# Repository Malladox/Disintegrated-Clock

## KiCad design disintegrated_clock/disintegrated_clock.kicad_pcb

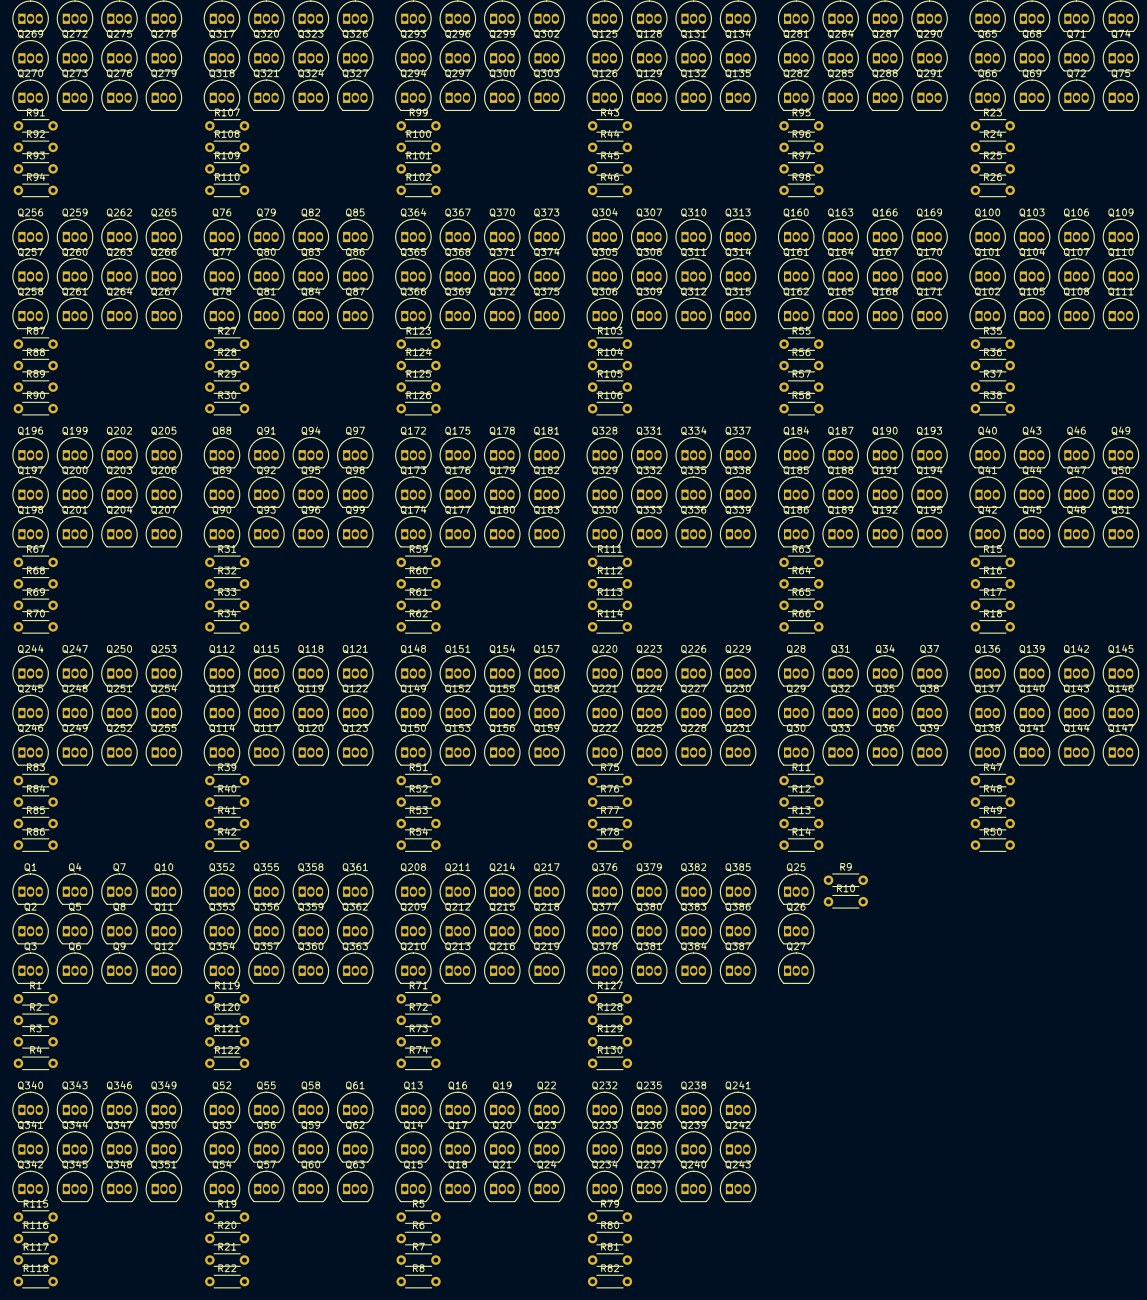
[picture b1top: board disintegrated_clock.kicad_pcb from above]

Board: 2 copper layers, 517 parts (0 on the bottom side), 421 nets, no tracks yet.

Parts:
Q1, Q2, Q3, Q4, Q5, Q6, Q7, Q8, Q9, Q10, Q11, Q12, Q13, Q14, Q15, Q16, Q17, Q18, Q19, Q20, Q21, Q22, Q23, Q24, Q25, Q26, Q27, Q28, Q29, Q30, Q31, Q32, Q33, Q34, Q35, Q36, Q37, Q38, Q39, Q40, Q41, Q42, Q43, Q44, Q45, Q46, Q47, Q48, Q49, Q50, Q51, Q52, Q53, Q54, Q55, Q56, Q57, Q58, Q59, Q60, Q61, Q62, Q63, Q64, Q65, Q66, Q67, Q68, Q69, Q70, Q71, Q72, Q73, Q74, Q75, Q76, Q77, Q78, Q79, Q80, Q81, Q82, Q83, Q84, Q85, Q86, Q87, Q88, Q89, Q90, Q91, Q92, Q93, Q94, Q95, Q96, Q97, Q98, Q99, Q100, Q101, Q102, Q103, Q104, Q105, Q106, Q107, Q108, Q109, Q110, Q111, Q112, Q113, Q114, Q115, Q116, Q117, Q118, Q119, Q120, Q121, Q122, Q123, Q124, Q125, Q126, Q127, Q128, Q129, Q130, Q131, Q132, Q133, Q134, Q135, Q136, Q137, Q138, Q139, Q140, Q141, Q142, Q143, Q144, Q145, Q146, Q147, Q148, Q149, Q150, Q151, Q152, Q153, Q154, Q155, Q156, Q157, Q158, Q159, Q160, Q161, Q162, Q163, Q164, Q165, Q166, Q167, Q168, Q169, Q170, Q171, Q172, Q173, Q174, Q175, Q176, Q177, Q178, Q179, Q180, Q181, Q182, Q183, Q184, Q185, Q186, Q187, Q188, Q189, Q190, Q191, Q192, Q193, Q194, Q195, Q196, Q197, Q198, Q199, Q200, Q201, Q202, Q203, Q204, Q205, Q206, Q207, Q208, Q209, Q210, Q211, Q212, Q213, Q214, Q215, Q216, Q217, Q218, Q219, Q220, Q221, Q222, Q223, Q224, Q225, Q226, Q227, Q228, Q229, Q230, Q231, Q232, Q233, Q234, Q235, Q236, Q237, Q238, Q239, Q240, Q241, Q242, Q243, Q244, Q245, Q246, Q247, Q248, Q249, Q250, Q251, Q252, Q253, Q254, Q255, Q256, Q257, Q258, Q259, Q260, Q261, Q262, Q263, Q264, Q265, Q266, Q267, Q268, Q269, Q270, Q271, Q272, Q273, Q274, Q275, Q276, Q277, Q278, Q279, Q280, Q281, Q282, Q283, Q284, Q285, Q286, Q287, Q288, Q289, Q290, Q291, Q292, Q293, Q294, Q295, Q296, Q297, Q298, Q299, Q300, Q301, Q302, Q303, Q304, Q305, Q306, Q307, Q308, Q309, Q310, Q311, Q312, Q313, Q314, Q315, Q316, Q317, Q318, Q319, Q320, Q321, Q322, Q323, Q324, Q325, Q326, Q327, Q328, Q329, Q330, Q331, Q332, Q333, Q334, Q335, Q336, Q337, Q338, Q339, Q340, Q341, Q342, Q343, Q344, Q345, Q346, Q347, Q348, Q349, Q350, Q351, Q352, Q353, Q354, Q355, Q356, Q357, Q358, Q359, Q360, Q361, Q362, Q363, Q364, Q365, Q366, Q367, Q368, Q369, Q370, Q371, Q372, Q373, Q374, Q375, Q376, Q377, Q378, Q379, Q380, Q381, Q382, Q383, Q384, Q385, Q386, Q387: 2N7000; TO-92_Inline
R1, R2, R3, R4, R5, R6, R7, R8, R9, R10, R11, R12, R13, R14, R15, R16, R17, R18, R19, R20, R21, R22, R23, R24, R25, R26, R27, R28, R29, R30, R31, R32, R33, R34, R35, R36, R37, R38, R39, R40, R41, R42, R43, R44, R45, R46, R47, R48, R49, R50, R51, R52, R53, R54, R55, R56, R57, R58, R59, R60, R61, R62, R63, R64, R65, R66, R67, R68, R69, R70, R71, R72, R73, R74, R75, R76, R77, R78, R79, R80, R81, R82, R83, R84, R85, R86, R87, R88, R89, R90, R91, R92, R93, R94, R95, R96, R97, R98, R99, R100, R101, R102, R103, R104, R105, R106, R107, R108, R109, R110, R111, R112, R113, R114, R115, R116, R117, R118, R119, R120, R121, R122, R123, R124, R125, R126, R127, R128, R129, R130: 10K; R_Axial_DIN0204_L3.6mm_D1.6mm_P5.08mm_Horizontal

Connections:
+5V: R1.1, R2.1, R3.1, R4.1, R5.1, R6.1, R7.1, R8.1, R9.1, R10.1, R11.1, R12.1, R13.1, R14.1, R15.1, R16.1, R17.1, R18.1, R19.1, R20.1, R21.1, R22.1, R23.1, R24.1, R25.1, R26.1, R27.1, R28.1, R29.1, R30.1, R31.1, R32.1, R33.1, R34.1, R35.1, R36.1, R37.1, R38.1, R39.1, R40.1, R41.1, R42.1, R43.1, R44.1, R45.1, R46.1, R47.1, R48.1, R49.1, R50.1, R51.1, R52.1, R53.1, R54.1, R55.1, R56.1, R57.1, R58.1, R59.1, R60.1, R61.1, R62.1, R63.1, R64.1, R65.1, R66.1, R67.1, R68.1, R69.1, R70.1, R71.1, R72.1, R73.1, R74.1, R75.1, R76.1, R77.1, R78.1, R79.1, R80.1, R81.1, R82.1, R83.1, R84.1, R85.1, R86.1, R87.1, R88.1, R89.1, R90.1, R91.1, R92.1, R93.1, R94.1, R95.1, R96.1, R97.1, R98.1, R99.1, R100.1, R101.1, R102.1, R103.1, R104.1, R105.1, R106.1, R107.1, R108.1, R109.1, R110.1, R111.1, R112.1, R113.1, R114.1, R115.1, R116.1, R117.1, R118.1, R119.1, R120.1, R121.1, R122.1, R123.1, R124.1, R125.1, R126.1, R127.1, R128.1, R129.1, R130.1
/and/out: Q27.3 (D), R10.2
/jk-flipflop2/!Q: Q1.2 (G), Q8.2 (G), Q10.3 (D), R4.2
/jk-flipflop2/Q: Q6.2 (G), Q7.3 (D), Q10.2 (G), R3.2
/jk-flipflop2/clk: Q3.2 (G), Q4.2 (G)
/jk-flipflop3/!Q: Q13.2 (G), Q20.2 (G), Q22.3 (D), R8.2
/jk-flipflop3/Q: Q18.2 (G), Q19.3 (D), Q22.2 (G), R7.2
/jk-flipflop3/clk: Q15.2 (G), Q16.2 (G)
/jk-flipflop4/!Q: Q28.2 (G), Q35.2 (G), Q37.3 (D), R14.2
/jk-flipflop4/Q: Q33.2 (G), Q34.3 (D), Q37.2 (G), R13.2
/jk-flipflop4/clk: Q30.2 (G), Q31.2 (G)
/jk-flipflop5/!Q: Q40.2 (G), Q47.2 (G), Q49.3 (D), R18.2
/jk-flipflop5/Q: Q45.2 (G), Q46.3 (D), Q49.2 (G), R17.2
/jk-flipflop5/clk: Q42.2 (G), Q43.2 (G)
/jk-flipflop6/!Q: Q52.2 (G), Q59.2 (G), Q61.3 (D), R22.2
/jk-flipflop6/Q: Q57.2 (G), Q58.3 (D), Q61.2 (G), R21.2
/jk-flipflop6/clk: Q54.2 (G), Q55.2 (G)
/jk-flipflop7/!Q: Q64.2 (G), Q71.2 (G), Q73.3 (D), R26.2
/jk-flipflop7/Q: Q69.2 (G), Q70.3 (D), Q73.2 (G), R25.2
/jk-flipflop7/clk: Q66.2 (G), Q67.2 (G)
/jk-flipflop8/!Q: Q76.2 (G), Q83.2 (G), Q85.3 (D), R30.2
/jk-flipflop8/Q: Q81.2 (G), Q82.3 (D), Q85.2 (G), R29.2
/jk-flipflop8/clk: Q78.2 (G), Q79.2 (G)
/jk-flipflop9/!Q: Q88.2 (G), Q95.2 (G), Q97.3 (D), R34.2
/jk-flipflop9/Q: Q93.2 (G), Q94.3 (D), Q97.2 (G), R33.2
/jk-flipflop9/clk: Q90.2 (G), Q91.2 (G)
/jk-flipflop10/!Q: Q100.2 (G), Q107.2 (G), Q109.3 (D), R38.2
/jk-flipflop10/Q: Q105.2 (G), Q106.3 (D), Q109.2 (G), R37.2
/jk-flipflop10/clk: Q102.2 (G), Q103.2 (G)
/jk-flipflop11/!Q: Q112.2 (G), Q119.2 (G), Q121.3 (D), R42.2
/jk-flipflop11/Q: Q117.2 (G), Q118.3 (D), Q121.2 (G), R41.2
/jk-flipflop11/clk: Q114.2 (G), Q115.2 (G)
/jk-flipflop12/!Q: Q124.2 (G), Q131.2 (G), Q133.3 (D), R46.2
/jk-flipflop12/Q: Q129.2 (G), Q130.3 (D), Q133.2 (G), R45.2
/jk-flipflop12/clk: Q126.2 (G), Q127.2 (G)
/jk-flipflop13/!Q: Q136.2 (G), Q143.2 (G), Q145.3 (D), R50.2
/jk-flipflop13/Q: Q141.2 (G), Q142.3 (D), Q145.2 (G), R49.2
/jk-flipflop13/clk: Q138.2 (G), Q139.2 (G)
/jk-flipflop14/!Q: Q148.2 (G), Q155.2 (G), Q157.3 (D), R54.2
/jk-flipflop14/Q: Q153.2 (G), Q154.3 (D), Q157.2 (G), R53.2
/jk-flipflop14/clk: Q150.2 (G), Q151.2 (G)
/jk-flipflop15/!Q: Q160.2 (G), Q167.2 (G), Q169.3 (D), R58.2
/jk-flipflop15/Q: Q165.2 (G), Q166.3 (D), Q169.2 (G), R57.2
/jk-flipflop15/clk: Q162.2 (G), Q163.2 (G)
/jk-flipflop16/!Q: Q172.2 (G), Q179.2 (G), Q181.3 (D), R62.2
/jk-flipflop16/Q: Q177.2 (G), Q178.3 (D), Q181.2 (G), R61.2
/jk-flipflop16/clk: Q174.2 (G), Q175.2 (G)
/jk-flipflop17/!Q: Q184.2 (G), Q191.2 (G), Q193.3 (D), R66.2
/jk-flipflop17/Q: Q189.2 (G), Q190.3 (D), Q193.2 (G), R65.2
/jk-flipflop17/clk: Q186.2 (G), Q187.2 (G)
/jk-flipflop18/!Q: Q196.2 (G), Q203.2 (G), Q205.3 (D), R70.2
/jk-flipflop18/Q: Q201.2 (G), Q202.3 (D), Q205.2 (G), R69.2
/jk-flipflop18/clk: Q198.2 (G), Q199.2 (G)
/jk-flipflop19/!Q: Q208.2 (G), Q215.2 (G), Q217.3 (D), R74.2
/jk-flipflop19/Q: Q213.2 (G), Q214.3 (D), Q217.2 (G), R73.2
/jk-flipflop19/clk: Q210.2 (G), Q211.2 (G)
/jk-flipflop20/!Q: Q220.2 (G), Q227.2 (G), Q229.3 (D), R78.2
/jk-flipflop20/Q: Q225.2 (G), Q226.3 (D), Q229.2 (G), R77.2
/jk-flipflop20/clk: Q222.2 (G), Q223.2 (G)
/jk-flipflop21/!Q: Q232.2 (G), Q239.2 (G), Q241.3 (D), R82.2
/jk-flipflop21/Q: Q237.2 (G), Q238.3 (D), Q241.2 (G), R81.2
/jk-flipflop21/clk: Q234.2 (G), Q235.2 (G)
/jk-flipflop22/!Q: Q244.2 (G), Q251.2 (G), Q253.3 (D), R86.2
/jk-flipflop22/Q: Q249.2 (G), Q250.3 (D), Q253.2 (G), R85.2
/jk-flipflop22/clk: Q246.2 (G), Q247.2 (G)
/jk-flipflop23/!Q: Q256.2 (G), Q263.2 (G), Q265.3 (D), R90.2
/jk-flipflop23/Q: Q261.2 (G), Q262.3 (D), Q265.2 (G), R89.2
/jk-flipflop23/clk: Q258.2 (G), Q259.2 (G)
/jk-flipflop24/!Q: Q268.2 (G), Q275.2 (G), Q277.3 (D), R94.2
/jk-flipflop24/Q: Q273.2 (G), Q274.3 (D), Q277.2 (G), R93.2
/jk-flipflop24/clk: Q270.2 (G), Q271.2 (G)
/jk-flipflop25/!Q: Q280.2 (G), Q287.2 (G), Q289.3 (D), R98.2
/jk-flipflop25/Q: Q285.2 (G), Q286.3 (D), Q289.2 (G), R97.2
/jk-flipflop25/clk: Q282.2 (G), Q283.2 (G)
/jk-flipflop26/!Q: Q292.2 (G), Q299.2 (G), Q301.3 (D), R102.2
/jk-flipflop26/Q: Q297.2 (G), Q298.3 (D), Q301.2 (G), R101.2
/jk-flipflop26/clk: Q294.2 (G), Q295.2 (G)
/jk-flipflop27/!Q: Q304.2 (G), Q311.2 (G), Q313.3 (D), R106.2
/jk-flipflop27/Q: Q309.2 (G), Q310.3 (D), Q313.2 (G), R105.2
/jk-flipflop27/clk: Q306.2 (G), Q307.2 (G)
/jk-flipflop28/!Q: Q316.2 (G), Q323.2 (G), Q325.3 (D), R110.2
/jk-flipflop28/Q: Q321.2 (G), Q322.3 (D), Q325.2 (G), R109.2
/jk-flipflop28/clk: Q318.2 (G), Q319.2 (G)
/jk-flipflop29/!Q: Q328.2 (G), Q335.2 (G), Q337.3 (D), R114.2
/jk-flipflop29/Q: Q333.2 (G), Q334.3 (D), Q337.2 (G), R113.2
/jk-flipflop29/clk: Q330.2 (G), Q331.2 (G)
/jk-flipflop30/!Q: Q340.2 (G), Q347.2 (G), Q349.3 (D), R118.2
/jk-flipflop30/Q: Q345.2 (G), Q346.3 (D), Q349.2 (G), R117.2
/jk-flipflop30/clk: Q342.2 (G), Q343.2 (G)
/jk-flipflop31/!Q: Q352.2 (G), Q359.2 (G), Q361.3 (D), R122.2
/jk-flipflop31/Q: Q357.2 (G), Q358.3 (D), Q361.2 (G), R121.2
/jk-flipflop31/clk: Q354.2 (G), Q355.2 (G)
/jk-flipflop32/!Q: Q364.2 (G), Q371.2 (G), Q373.3 (D), R126.2
/jk-flipflop32/Q: Q369.2 (G), Q370.3 (D), Q373.2 (G), R125.2
/jk-flipflop32/clk: Q366.2 (G), Q367.2 (G)
/jk-flipflop33/!Q: Q376.2 (G), Q383.2 (G), Q385.3 (D), R130.2
/jk-flipflop33/Q: Q381.2 (G), Q382.3 (D), Q385.2 (G), R129.2
/jk-flipflop33/clk: Q378.2 (G), Q379.2 (G)
GND: Q3.1 (S), Q6.1 (S), Q9.1 (S), Q12.1 (S), Q15.1 (S), Q18.1 (S), Q21.1 (S), Q24.1 (S), Q26.1 (S), Q27.1 (S), Q30.1 (S), Q33.1 (S), Q36.1 (S), Q39.1 (S), Q42.1 (S), Q45.1 (S), Q48.1 (S), Q51.1 (S), Q54.1 (S), Q57.1 (S), Q60.1 (S), Q63.1 (S), Q66.1 (S), Q69.1 (S), Q72.1 (S), Q75.1 (S), Q78.1 (S), Q81.1 (S), Q84.1 (S), Q87.1 (S), Q90.1 (S), Q93.1 (S), Q96.1 (S), Q99.1 (S), Q102.1 (S), Q105.1 (S), Q108.1 (S), Q111.1 (S), Q114.1 (S), Q117.1 (S), Q120.1 (S), Q123.1 (S), Q126.1 (S), Q129.1 (S), Q132.1 (S), Q135.1 (S), Q138.1 (S), Q141.1 (S), Q144.1 (S), Q147.1 (S), Q150.1 (S), Q153.1 (S), Q156.1 (S), Q159.1 (S), Q162.1 (S), Q165.1 (S), Q168.1 (S), Q171.1 (S), Q174.1 (S), Q177.1 (S), Q180.1 (S), Q183.1 (S), Q186.1 (S), Q189.1 (S), Q192.1 (S), Q195.1 (S), Q198.1 (S), Q201.1 (S), Q204.1 (S), Q207.1 (S), Q210.1 (S), Q213.1 (S), Q216.1 (S), Q219.1 (S), Q222.1 (S), Q225.1 (S), Q228.1 (S), Q231.1 (S), Q234.1 (S), Q237.1 (S), Q240.1 (S), Q243.1 (S), Q246.1 (S), Q249.1 (S), Q252.1 (S), Q255.1 (S), Q258.1 (S), Q261.1 (S), Q264.1 (S), Q267.1 (S), Q270.1 (S), Q273.1 (S), Q276.1 (S), Q279.1 (S), Q282.1 (S), Q285.1 (S), Q288.1 (S), Q291.1 (S), Q294.1 (S), Q297.1 (S), Q300.1 (S), Q303.1 (S), Q306.1 (S), Q309.1 (S), Q312.1 (S), Q315.1 (S), Q318.1 (S), Q321.1 (S), Q324.1 (S), Q327.1 (S), Q330.1 (S), Q333.1 (S), Q336.1 (S), Q339.1 (S), Q342.1 (S), Q345.1 (S), Q348.1 (S), Q351.1 (S), Q354.1 (S), Q357.1 (S), Q360.1 (S), Q363.1 (S), Q366.1 (S), Q369.1 (S), Q372.1 (S), Q375.1 (S), Q378.1 (S), Q381.1 (S), Q384.1 (S), Q387.1 (S)
unnamed: Q1.3 (D), Q7.2 (G), R1.2
unnamed: Q1.1 (S), Q2.3 (D)
unnamed: Q2.1 (S), Q3.3 (D)
unnamed: Q4.1 (S), Q5.3 (D)
unnamed: Q5.1 (S), Q6.3 (D)
unnamed: Q7.1 (S), Q8.3 (D)
unnamed: Q8.1 (S), Q9.3 (D)
unnamed: Q10.1 (S), Q11.3 (D)
unnamed: Q4.3 (D), Q11.2 (G), R2.2
unnamed: Q11.1 (S), Q12.3 (D)
unnamed: Q13.3 (D), Q19.2 (G), R5.2
unnamed: Q13.1 (S), Q14.3 (D)
unnamed: Q14.1 (S), Q15.3 (D)
unnamed: Q16.3 (D), Q23.2 (G), R6.2
unnamed: Q16.1 (S), Q17.3 (D)
unnamed: Q17.1 (S), Q18.3 (D)
unnamed: Q19.1 (S), Q20.3 (D)
unnamed: Q20.1 (S), Q21.3 (D)
unnamed: Q22.1 (S), Q23.3 (D)
unnamed: Q23.1 (S), Q24.3 (D)
unnamed: Q25.3 (D), Q27.2 (G), R9.2
unnamed: Q25.1 (S), Q26.3 (D)
unnamed: Q28.3 (D), Q34.2 (G), R11.2
unnamed: Q28.1 (S), Q29.3 (D)
unnamed: Q29.1 (S), Q30.3 (D)
unnamed: Q31.3 (D), Q38.2 (G), R12.2
unnamed: Q31.1 (S), Q32.3 (D)
unnamed: Q32.1 (S), Q33.3 (D)
unnamed: Q34.1 (S), Q35.3 (D)
unnamed: Q35.1 (S), Q36.3 (D)
unnamed: Q37.1 (S), Q38.3 (D)
unnamed: Q38.1 (S), Q39.3 (D)
unnamed: Q40.3 (D), Q46.2 (G), R15.2
unnamed: Q40.1 (S), Q41.3 (D)
unnamed: Q41.1 (S), Q42.3 (D)
unnamed: Q43.3 (D), Q50.2 (G), R16.2
unnamed: Q43.1 (S), Q44.3 (D)
unnamed: Q44.1 (S), Q45.3 (D)
unnamed: Q46.1 (S), Q47.3 (D)
unnamed: Q47.1 (S), Q48.3 (D)
unnamed: Q49.1 (S), Q50.3 (D)
unnamed: Q50.1 (S), Q51.3 (D)
unnamed: Q52.3 (D), Q58.2 (G), R19.2
unnamed: Q52.1 (S), Q53.3 (D)
unnamed: Q53.1 (S), Q54.3 (D)
unnamed: Q55.3 (D), Q62.2 (G), R20.2
unnamed: Q55.1 (S), Q56.3 (D)
unnamed: Q56.1 (S), Q57.3 (D)
unnamed: Q58.1 (S), Q59.3 (D)
unnamed: Q59.1 (S), Q60.3 (D)
unnamed: Q61.1 (S), Q62.3 (D)
unnamed: Q62.1 (S), Q63.3 (D)
unnamed: Q64.3 (D), Q70.2 (G), R23.2
unnamed: Q64.1 (S), Q65.3 (D)
unnamed: Q65.1 (S), Q66.3 (D)
unnamed: Q67.3 (D), Q74.2 (G), R24.2
unnamed: Q67.1 (S), Q68.3 (D)
unnamed: Q68.1 (S), Q69.3 (D)
unnamed: Q70.1 (S), Q71.3 (D)
unnamed: Q71.1 (S), Q72.3 (D)
unnamed: Q73.1 (S), Q74.3 (D)
unnamed: Q74.1 (S), Q75.3 (D)
unnamed: Q76.3 (D), Q82.2 (G), R27.2
unnamed: Q76.1 (S), Q77.3 (D)
unnamed: Q77.1 (S), Q78.3 (D)
unnamed: Q79.3 (D), Q86.2 (G), R28.2
unnamed: Q79.1 (S), Q80.3 (D)
unnamed: Q80.1 (S), Q81.3 (D)
unnamed: Q82.1 (S), Q83.3 (D)
unnamed: Q83.1 (S), Q84.3 (D)
unnamed: Q85.1 (S), Q86.3 (D)
unnamed: Q86.1 (S), Q87.3 (D)
unnamed: Q88.3 (D), Q94.2 (G), R31.2
unnamed: Q88.1 (S), Q89.3 (D)
unnamed: Q89.1 (S), Q90.3 (D)
unnamed: Q91.3 (D), Q98.2 (G), R32.2
unnamed: Q91.1 (S), Q92.3 (D)
unnamed: Q92.1 (S), Q93.3 (D)
unnamed: Q94.1 (S), Q95.3 (D)
unnamed: Q95.1 (S), Q96.3 (D)
unnamed: Q97.1 (S), Q98.3 (D)
unnamed: Q98.1 (S), Q99.3 (D)
unnamed: Q100.3 (D), Q106.2 (G), R35.2
unnamed: Q100.1 (S), Q101.3 (D)
unnamed: Q101.1 (S), Q102.3 (D)
unnamed: Q103.3 (D), Q110.2 (G), R36.2
unnamed: Q103.1 (S), Q104.3 (D)
unnamed: Q104.1 (S), Q105.3 (D)
unnamed: Q106.1 (S), Q107.3 (D)
unnamed: Q107.1 (S), Q108.3 (D)
unnamed: Q109.1 (S), Q110.3 (D)
unnamed: Q110.1 (S), Q111.3 (D)
unnamed: Q112.3 (D), Q118.2 (G), R39.2
unnamed: Q112.1 (S), Q113.3 (D)
unnamed: Q113.1 (S), Q114.3 (D)
unnamed: Q115.3 (D), Q122.2 (G), R40.2
unnamed: Q115.1 (S), Q116.3 (D)
unnamed: Q116.1 (S), Q117.3 (D)
unnamed: Q118.1 (S), Q119.3 (D)
unnamed: Q119.1 (S), Q120.3 (D)
unnamed: Q121.1 (S), Q122.3 (D)
unnamed: Q122.1 (S), Q123.3 (D)
unnamed: Q124.3 (D), Q130.2 (G), R43.2
unnamed: Q124.1 (S), Q125.3 (D)
unnamed: Q125.1 (S), Q126.3 (D)
unnamed: Q127.3 (D), Q134.2 (G), R44.2
unnamed: Q127.1 (S), Q128.3 (D)
unnamed: Q128.1 (S), Q129.3 (D)
unnamed: Q130.1 (S), Q131.3 (D)
unnamed: Q131.1 (S), Q132.3 (D)
unnamed: Q133.1 (S), Q134.3 (D)
unnamed: Q134.1 (S), Q135.3 (D)
unnamed: Q136.3 (D), Q142.2 (G), R47.2
unnamed: Q136.1 (S), Q137.3 (D)
unnamed: Q137.1 (S), Q138.3 (D)
unnamed: Q139.3 (D), Q146.2 (G), R48.2
unnamed: Q139.1 (S), Q140.3 (D)
unnamed: Q140.1 (S), Q141.3 (D)
unnamed: Q142.1 (S), Q143.3 (D)
unnamed: Q143.1 (S), Q144.3 (D)
unnamed: Q145.1 (S), Q146.3 (D)
unnamed: Q146.1 (S), Q147.3 (D)
unnamed: Q148.3 (D), Q154.2 (G), R51.2
unnamed: Q148.1 (S), Q149.3 (D)
unnamed: Q149.1 (S), Q150.3 (D)
unnamed: Q151.3 (D), Q158.2 (G), R52.2
unnamed: Q151.1 (S), Q152.3 (D)
unnamed: Q152.1 (S), Q153.3 (D)
unnamed: Q154.1 (S), Q155.3 (D)
unnamed: Q155.1 (S), Q156.3 (D)
unnamed: Q157.1 (S), Q158.3 (D)
unnamed: Q158.1 (S), Q159.3 (D)
unnamed: Q160.3 (D), Q166.2 (G), R55.2
unnamed: Q160.1 (S), Q161.3 (D)
unnamed: Q161.1 (S), Q162.3 (D)
unnamed: Q163.3 (D), Q170.2 (G), R56.2
unnamed: Q163.1 (S), Q164.3 (D)
unnamed: Q164.1 (S), Q165.3 (D)
unnamed: Q166.1 (S), Q167.3 (D)
unnamed: Q167.1 (S), Q168.3 (D)
unnamed: Q169.1 (S), Q170.3 (D)
unnamed: Q170.1 (S), Q171.3 (D)
unnamed: Q172.3 (D), Q178.2 (G), R59.2
unnamed: Q172.1 (S), Q173.3 (D)
unnamed: Q173.1 (S), Q174.3 (D)
unnamed: Q175.3 (D), Q182.2 (G), R60.2
unnamed: Q175.1 (S), Q176.3 (D)
unnamed: Q176.1 (S), Q177.3 (D)
unnamed: Q178.1 (S), Q179.3 (D)
unnamed: Q179.1 (S), Q180.3 (D)
unnamed: Q181.1 (S), Q182.3 (D)
unnamed: Q182.1 (S), Q183.3 (D)
unnamed: Q184.3 (D), Q190.2 (G), R63.2
unnamed: Q184.1 (S), Q185.3 (D)
unnamed: Q185.1 (S), Q186.3 (D)
unnamed: Q187.3 (D), Q194.2 (G), R64.2
unnamed: Q187.1 (S), Q188.3 (D)
unnamed: Q188.1 (S), Q189.3 (D)
unnamed: Q190.1 (S), Q191.3 (D)
unnamed: Q191.1 (S), Q192.3 (D)
unnamed: Q193.1 (S), Q194.3 (D)
unnamed: Q194.1 (S), Q195.3 (D)
unnamed: Q196.3 (D), Q202.2 (G), R67.2
unnamed: Q196.1 (S), Q197.3 (D)
unnamed: Q197.1 (S), Q198.3 (D)
unnamed: Q199.3 (D), Q206.2 (G), R68.2
unnamed: Q199.1 (S), Q200.3 (D)
unnamed: Q200.1 (S), Q201.3 (D)
unnamed: Q202.1 (S), Q203.3 (D)
unnamed: Q203.1 (S), Q204.3 (D)
unnamed: Q205.1 (S), Q206.3 (D)
unnamed: Q206.1 (S), Q207.3 (D)
unnamed: Q208.3 (D), Q214.2 (G), R71.2
unnamed: Q208.1 (S), Q209.3 (D)
unnamed: Q209.1 (S), Q210.3 (D)
unnamed: Q211.3 (D), Q218.2 (G), R72.2
unnamed: Q211.1 (S), Q212.3 (D)
unnamed: Q212.1 (S), Q213.3 (D)
unnamed: Q214.1 (S), Q215.3 (D)
unnamed: Q215.1 (S), Q216.3 (D)
unnamed: Q217.1 (S), Q218.3 (D)
unnamed: Q218.1 (S), Q219.3 (D)
unnamed: Q220.3 (D), Q226.2 (G), R75.2
unnamed: Q220.1 (S), Q221.3 (D)
unnamed: Q221.1 (S), Q222.3 (D)
unnamed: Q223.3 (D), Q230.2 (G), R76.2
unnamed: Q223.1 (S), Q224.3 (D)
unnamed: Q224.1 (S), Q225.3 (D)
unnamed: Q226.1 (S), Q227.3 (D)
unnamed: Q227.1 (S), Q228.3 (D)
unnamed: Q229.1 (S), Q230.3 (D)
unnamed: Q230.1 (S), Q231.3 (D)
unnamed: Q232.3 (D), Q238.2 (G), R79.2
unnamed: Q232.1 (S), Q233.3 (D)
unnamed: Q233.1 (S), Q234.3 (D)
unnamed: Q235.3 (D), Q242.2 (G), R80.2
unnamed: Q235.1 (S), Q236.3 (D)
unnamed: Q236.1 (S), Q237.3 (D)
unnamed: Q238.1 (S), Q239.3 (D)
unnamed: Q239.1 (S), Q240.3 (D)
unnamed: Q241.1 (S), Q242.3 (D)
unnamed: Q242.1 (S), Q243.3 (D)
unnamed: Q244.3 (D), Q250.2 (G), R83.2
unnamed: Q244.1 (S), Q245.3 (D)
unnamed: Q245.1 (S), Q246.3 (D)
unnamed: Q247.3 (D), Q254.2 (G), R84.2
unnamed: Q247.1 (S), Q248.3 (D)
unnamed: Q248.1 (S), Q249.3 (D)
unnamed: Q250.1 (S), Q251.3 (D)
unnamed: Q251.1 (S), Q252.3 (D)
unnamed: Q253.1 (S), Q254.3 (D)
unnamed: Q254.1 (S), Q255.3 (D)
unnamed: Q256.3 (D), Q262.2 (G), R87.2
unnamed: Q256.1 (S), Q257.3 (D)
unnamed: Q257.1 (S), Q258.3 (D)
unnamed: Q259.3 (D), Q266.2 (G), R88.2
unnamed: Q259.1 (S), Q260.3 (D)
unnamed: Q260.1 (S), Q261.3 (D)
unnamed: Q262.1 (S), Q263.3 (D)
unnamed: Q263.1 (S), Q264.3 (D)
unnamed: Q265.1 (S), Q266.3 (D)
unnamed: Q266.1 (S), Q267.3 (D)
unnamed: Q268.3 (D), Q274.2 (G), R91.2
unnamed: Q268.1 (S), Q269.3 (D)
unnamed: Q269.1 (S), Q270.3 (D)
unnamed: Q271.3 (D), Q278.2 (G), R92.2
unnamed: Q271.1 (S), Q272.3 (D)
unnamed: Q272.1 (S), Q273.3 (D)
unnamed: Q274.1 (S), Q275.3 (D)
unnamed: Q275.1 (S), Q276.3 (D)
unnamed: Q277.1 (S), Q278.3 (D)
unnamed: Q278.1 (S), Q279.3 (D)
unnamed: Q280.3 (D), Q286.2 (G), R95.2
unnamed: Q280.1 (S), Q281.3 (D)
unnamed: Q281.1 (S), Q282.3 (D)
unnamed: Q283.3 (D), Q290.2 (G), R96.2
unnamed: Q283.1 (S), Q284.3 (D)
unnamed: Q284.1 (S), Q285.3 (D)
unnamed: Q286.1 (S), Q287.3 (D)
unnamed: Q287.1 (S), Q288.3 (D)
unnamed: Q289.1 (S), Q290.3 (D)
unnamed: Q290.1 (S), Q291.3 (D)
unnamed: Q292.3 (D), Q298.2 (G), R99.2
unnamed: Q292.1 (S), Q293.3 (D)
unnamed: Q293.1 (S), Q294.3 (D)
unnamed: Q295.3 (D), Q302.2 (G), R100.2
unnamed: Q295.1 (S), Q296.3 (D)
unnamed: Q296.1 (S), Q297.3 (D)
unnamed: Q298.1 (S), Q299.3 (D)
unnamed: Q299.1 (S), Q300.3 (D)
unnamed: Q301.1 (S), Q302.3 (D)
unnamed: Q302.1 (S), Q303.3 (D)
unnamed: Q304.3 (D), Q310.2 (G), R103.2
unnamed: Q304.1 (S), Q305.3 (D)
unnamed: Q305.1 (S), Q306.3 (D)
unnamed: Q307.3 (D), Q314.2 (G), R104.2
unnamed: Q307.1 (S), Q308.3 (D)
unnamed: Q308.1 (S), Q309.3 (D)
unnamed: Q310.1 (S), Q311.3 (D)
unnamed: Q311.1 (S), Q312.3 (D)
unnamed: Q313.1 (S), Q314.3 (D)
unnamed: Q314.1 (S), Q315.3 (D)
unnamed: Q316.3 (D), Q322.2 (G), R107.2
unnamed: Q316.1 (S), Q317.3 (D)
unnamed: Q317.1 (S), Q318.3 (D)
unnamed: Q319.3 (D), Q326.2 (G), R108.2
unnamed: Q319.1 (S), Q320.3 (D)
unnamed: Q320.1 (S), Q321.3 (D)
unnamed: Q322.1 (S), Q323.3 (D)
unnamed: Q323.1 (S), Q324.3 (D)
unnamed: Q325.1 (S), Q326.3 (D)
unnamed: Q326.1 (S), Q327.3 (D)
unnamed: Q328.3 (D), Q334.2 (G), R111.2
unnamed: Q328.1 (S), Q329.3 (D)
unnamed: Q329.1 (S), Q330.3 (D)
unnamed: Q331.3 (D), Q338.2 (G), R112.2
unnamed: Q331.1 (S), Q332.3 (D)
unnamed: Q332.1 (S), Q333.3 (D)
unnamed: Q334.1 (S), Q335.3 (D)
unnamed: Q335.1 (S), Q336.3 (D)
unnamed: Q337.1 (S), Q338.3 (D)
unnamed: Q338.1 (S), Q339.3 (D)
unnamed: Q340.3 (D), Q346.2 (G), R115.2
unnamed: Q340.1 (S), Q341.3 (D)
unnamed: Q341.1 (S), Q342.3 (D)
unnamed: Q343.3 (D), Q350.2 (G), R116.2
unnamed: Q343.1 (S), Q344.3 (D)
unnamed: Q344.1 (S), Q345.3 (D)
unnamed: Q346.1 (S), Q347.3 (D)
unnamed: Q347.1 (S), Q348.3 (D)
unnamed: Q349.1 (S), Q350.3 (D)
unnamed: Q350.1 (S), Q351.3 (D)
unnamed: Q352.3 (D), Q358.2 (G), R119.2
unnamed: Q352.1 (S), Q353.3 (D)
unnamed: Q353.1 (S), Q354.3 (D)
unnamed: Q355.3 (D), Q362.2 (G), R120.2
unnamed: Q355.1 (S), Q356.3 (D)
unnamed: Q356.1 (S), Q357.3 (D)
unnamed: Q358.1 (S), Q359.3 (D)
unnamed: Q359.1 (S), Q360.3 (D)
unnamed: Q361.1 (S), Q362.3 (D)
unnamed: Q362.1 (S), Q363.3 (D)
unnamed: Q364.3 (D), Q370.2 (G), R123.2
unnamed: Q364.1 (S), Q365.3 (D)
unnamed: Q365.1 (S), Q366.3 (D)
unnamed: Q367.3 (D), Q374.2 (G), R124.2
unnamed: Q367.1 (S), Q368.3 (D)
unnamed: Q368.1 (S), Q369.3 (D)
unnamed: Q370.1 (S), Q371.3 (D)
unnamed: Q371.1 (S), Q372.3 (D)
unnamed: Q373.1 (S), Q374.3 (D)
unnamed: Q374.1 (S), Q375.3 (D)
unnamed: Q376.3 (D), Q382.2 (G), R127.2
unnamed: Q376.1 (S), Q377.3 (D)
unnamed: Q377.1 (S), Q378.3 (D)
unnamed: Q379.3 (D), Q386.2 (G), R128.2
unnamed: Q379.1 (S), Q380.3 (D)
unnamed: Q380.1 (S), Q381.3 (D)
unnamed: Q382.1 (S), Q383.3 (D)
unnamed: Q383.1 (S), Q384.3 (D)
unnamed: Q385.1 (S), Q386.3 (D)
unnamed: Q386.1 (S), Q387.3 (D)

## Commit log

2024-03-23 Initial commit to github
